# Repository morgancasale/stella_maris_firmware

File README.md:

# Rehabilitation Devices for One-Handed Interaction

This project focuses on the design and development of compact rehabilitation devices intended for children who cannot use one hand. The goal is to provide engaging physical objects that help stimulate motor activity and interaction during therapy exercises.

The devices integrate sensing, actuation, and wireless communication in a very compact form factor.

---

## Project Overview

Each device contains:

- **Electromagnets** used for actuation and interaction with the patients  
- **Time-of-Flight (ToF) sensors** to detect the distance from patients  
- A **Seeed Studio XIAO ESP32-C6** microcontroller for control and wireless communication  

The devices communicate wirelessly and interact with a browser-based interface, allowing therapists or developers to monitor and control the system.

---

## Features

- Embedded firmware for **ESP32-C6**
- **Bluetooth Low Energy (BLE)** interface for communication with a JavaScript web application
- **ESP-NOW mesh-style communication** enabling multiple devices to exchange data with each other
- Integration of multiple sensors and electromagnets in a constrained physical space
- Designed for **low-power embedded operation**

---

## System Architecture

The system consists of three main layers.

### Embedded Device

Each device runs firmware on the **XIAO ESP32-C6** that:

- Reads data from ToF sensors  
- Controls electromagnets  
- Communicates with other devices using ESP-NOW  
- Exposes BLE services for external control  

### Device-to-Device Communication

Devices use **ESP-NOW** to exchange messages, enabling cooperative behaviors between multiple rehabilitation objects without requiring a central router.

### Web Interface

A **JavaScript-based interface** connects to the devices through **Bluetooth Low Energy (BLE)** to:

- Monitor device status  
- Send control commands  
- Configure behaviors  

---

## Hardware

Main components:

- **XIAO ESP32-C6**
- **Time-of-Flight (ToF) distance sensors**
- **Electromagnets**
- Custom compact enclosure designed to fit all components

The design focuses on integrating all components into a very small footprint suitable for small handheld objects.

---

## PCB Design

A custom PCB was designed to integrate all the electronic components into a compact form factor suitable for the rehabilitation devices.

The board includes:

- Pass through holes to solder a **Seeed Studio XIAO ESP32-C6**
- Drivers for the **electromagnets**
- Interfaces for **Time-of-Flight (ToF) sensors**
- Power management and protection circuitry
- Connectors for sensors and actuators

The PCB was designed to minimize size while keeping the system reliable and easy to assemble inside the small enclosure used by the devices.

---

## Firmware Responsibilities

The firmware handles:

- Sensor acquisition  
- Electromagnet control  
- BLE communication with the web interface  
- ESP-NOW messaging between devices  
- Resource management for a compact embedded system  

---

## Repository Structure

```
.
├── firmware/
│   └── ESP32-C6 firmware source
│
├── web-interface/
│   └── JavaScript BLE interface
│
├── hardware/
│   └── Hardware integration notes and schematics
```

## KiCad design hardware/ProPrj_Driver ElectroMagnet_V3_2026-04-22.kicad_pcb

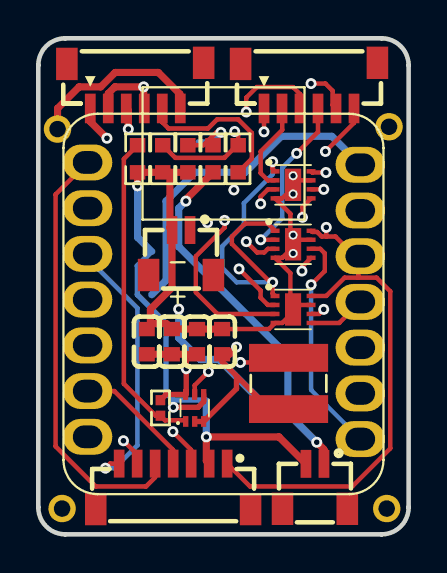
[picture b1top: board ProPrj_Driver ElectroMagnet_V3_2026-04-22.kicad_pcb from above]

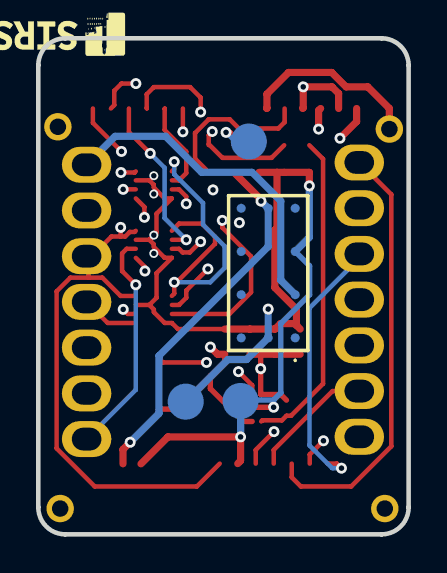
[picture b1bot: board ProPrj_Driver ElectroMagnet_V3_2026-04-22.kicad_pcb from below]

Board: 4 copper layers, 20.6 x 27.6 mm, 25 parts (4 on the bottom side), 28 nets.

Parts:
BAT+: pogo_pin_pad
BAT-: pogo_pin_pad
BATT: CONN-TH_BM02B-SRSS-TB-LF-SN
BUTT: CONN-SMD_BM06B-SRSS-TBT-LF-SN
C1, C2, C3, C4: C0603
CONV: SOT-563_L1.6-W1.2-P0.50-LS1.6-BR
EM: CONN-SMD_BM06B-SRSS-TBT-LF-SN
EXT_USB: CONN-TH_BM02B-SRSS-TB-LF-SN
I2C_TOF: CONN-SMD_7P-P1.00_BM07B-SRSS-TB
L1: IND-SMD_L4.1-W4.1_SPM40XX
R1: R0402
R2, R3, R4, R5, R6: R0603
RELAYS: CRR031AS
SENSE_POGO: pogo_pin_pad
U4, U5, U6: WSON-8_L2.0-W2.0-P0.50-BL-EP_DSG
XIAO_ESP32C6: MOUDLE14P-SMD-2.54-21X17.8MM

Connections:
3V3: I2C_TOF.1, R5.2, R6.2, U4.8, U5.8, U6.8, XIAO_ESP32C6.12
5V: C2.1, C3.1, C4.1, CONV.6, R1.2, U4.1, U5.1, U6.1
$1N5409: CONV.5, L1.2
$1N5536: CONV.1, R1.1, R2.2
$1N33122: BUTT.5, R5.1
BAT+: BATT.1, BUTT.3, R3.1, RELAYS.5
BAT_SENSE: R3.2, R4.1, SENSE_POGO.1
EM_BAT+: BUTT.1, C1.1, CONV.2, CONV.3, L1.1
EM_OUT_NEG1: EM.1, U4.3
EM_OUT_NEG2: EM.3, U5.3
EM_OUT_NEG3: EM.5, U6.3
EM_OUT_POS1: EM.2, U4.2
EM_OUT_POS2: EM.4, U5.2
EM_OUT_POS3: EM.6, U6.2
EM_PWM_A_1: U4.6, XIAO_ESP32C6.4
EM_PWM_A_2: U5.6, XIAO_ESP32C6.8
EM_PWM_A_3: U6.6, XIAO_ESP32C6.10
EM_PWM_B_1: U4.5, XIAO_ESP32C6.7
EM_PWM_B_2: U5.5, XIAO_ESP32C6.9
EM_PWM_B_3: U6.5, XIAO_ESP32C6.11
GND: BAT-.1, BATT.2, BUTT.6, C1.2, C2.2, C3.2, C4.2, CONV.4, EXT_USB.2, I2C_TOF.2, R2.1, R4.2, R6.1, RELAYS.3, U4.4, U4.7, U4.9, U5.4, U5.7, U5.9, U6.4, U6.7, U6.9, XIAO_ESP32C6.13
POGO_BAT+: BAT+.1, BUTT.2, BUTT.4, RELAYS.10
SCL: I2C_TOF.4, XIAO_ESP32C6.6
SDA: I2C_TOF.3, XIAO_ESP32C6.5
TOF_1: I2C_TOF.5, XIAO_ESP32C6.1
TOF_2: I2C_TOF.6, XIAO_ESP32C6.2
TOF_3: I2C_TOF.7, XIAO_ESP32C6.3
V_BUS: RELAYS.2, XIAO_ESP32C6.14

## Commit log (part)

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2024-12-10 Arduino libraries fix
2024-12-10 Controller button fix with electromagnets
2024-12-30 Added BLE characteristic to update interface of device's electromagnet state
2026-04-22 Cleaning up old code
2026-04-22 Add README
2026-04-22 adding things
